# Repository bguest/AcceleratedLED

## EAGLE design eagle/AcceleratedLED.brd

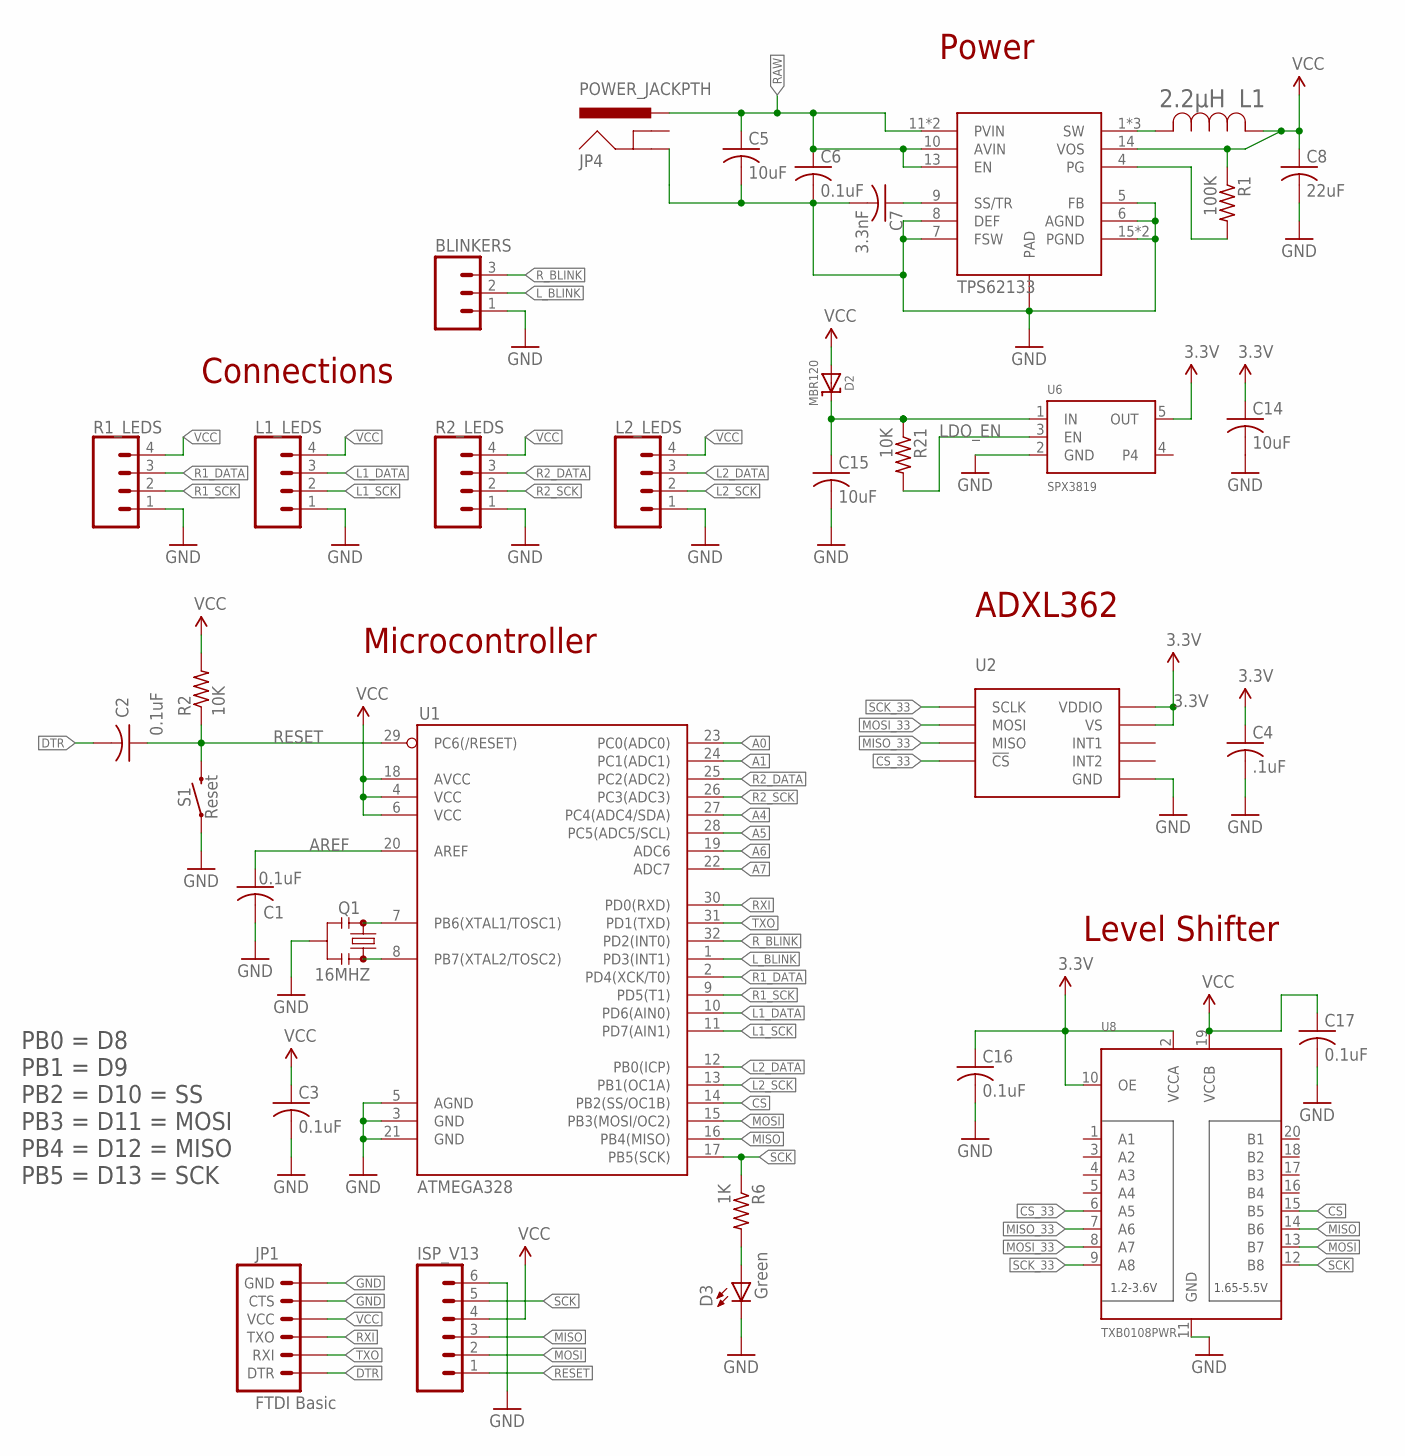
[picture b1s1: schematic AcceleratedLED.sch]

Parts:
BLINKERS: M03JST-PTH; JST-3-PTH
C1, C2, C3, C6, C16, C17: 0.1uF; C0805
C4: .1uF; C0805
C5, C14, C15: 10uF; C0805
C7: 3.3nF; C0805
C8: 22uF; C0805
D2: MBR120; SOD-123
D3: Green; CHIPLED_0805
IC1: TPS62133; QFN16
ISP_V13: M06SIP; 1X06
JP1: FTDI Basic; 1X06
JP4: POWER_JACKPTH; POWER_JACK_PTH
L1: 2.2μH; IND_IHLP-1212BZ-L
L1_LEDS, L2_LEDS: CONN_04JST-PTH; JST-4-PTH
Q1: 16MHZ; RESONATOR-SMD
R1: 100K; M0805
R1_LEDS, R2_LEDS: CONN_04JST-PTH; JST-4-PTH
R2, R21: 10K; M0805
R6: 1K; M0805
S1: Reset; TACTILE_SWITCH_SMD_5.2MM
U1: ATMEGA328; TQFP32-08
U2: ADXL362ADXL362-1:1; ADXL362-1:1
U6: SPX3819; SOT23-5
U8: TXB0108PWR; TSSOP20

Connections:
3.3V: C4.1, C14.1, C16.1, U2.P$1 (VDDIO), U2.P$14 (VS), U6.5 (OUT), U8.2 (VCCA), U8.10 (OE)
A0: U1.23 (PC0(ADC0))
A1: U1.24 (PC1(ADC1))
A4: U1.27 (PC4(ADC4/SDA))
A5: U1.28 (PC5(ADC5/SCL))
A6: U1.19 (ADC6)
A7: U1.22 (ADC7)
AREF: C1.1, U1.20 (AREF)
CS: U1.14 (PB2(SS/OC1B)), U8.15 (B5)
CS_33: U2.P$8 (!CS), U8.6 (A5)
DTR: C2.2, JP1.1 (DTR)
GND: BLINKERS.1, C1.2, C3.2, C4.2, C5.2, C6.2, C7.2, C8.2, C14.2, C15.2, C16.2, C17.2, D3.C, IC1.5 (FB), IC1.6 (AGND), IC1.7 (FSW), IC1.8 (DEF), IC1.15 (PGND), IC1.16 (PGND), IC1.PAD, ISP_V13.6, JP1.5 (CTS), JP1.6 (GND), JP4.GND, L1_LEDS.1, L2_LEDS.1, Q1.2, R1_LEDS.1, R2_LEDS.1, S1.1, S1.2 (1), U1.3 (GND), U1.5 (AGND), U1.21 (GND), U2.P$12 (GND), U2.P$13 (GND), U2.P$16 (GND), U6.2 (GND), U8.11 (GND)
L1_DATA: L1_LEDS.3, U1.10 (PD6(AIN0))
L1_SCK: L1_LEDS.2, U1.11 (PD7(AIN1))
L2_DATA: L2_LEDS.3, U1.12 (PB0(ICP))
L2_SCK: L2_LEDS.2, U1.13 (PB1(OC1A))
LDO_EN: R21.2, U6.3 (EN)
L_BLINK: BLINKERS.2, U1.1 (PD3(INT1))
MISO: ISP_V13.3, U1.16 (PB4(MISO)), U8.14 (B6)
MISO_33: U2.P$7 (MISO), U8.7 (A6)
MOSI: ISP_V13.2, U1.15 (PB3(MOSI/OC2)), U8.13 (B7)
MOSI_33: U2.P$6 (MOSI), U8.8 (A7)
unnamed: Q1.3, U1.8 (PB7(XTAL2/TOSC2))
unnamed: Q1.1, U1.7 (PB6(XTAL1/TOSC1))
unnamed: D3.A, R6.2
unnamed: C15.1, D2.C, R21.1, U6.1 (IN)
PG: IC1.4 (PG), R1.2
R1_DATA: R1_LEDS.3, U1.2 (PD4(XCK/T0))
R1_SCK: R1_LEDS.2, U1.9 (PD5(T1))
R2_DATA: R2_LEDS.3, U1.25 (PC2(ADC2))
R2_SCK: R2_LEDS.2, U1.26 (PC3(ADC3))
RAW: C5.1, C6.1, IC1.10 (AVIN), IC1.11 (PVIN), IC1.12 (PVIN), IC1.13 (EN), JP4.PWR
RESET: C2.1, ISP_V13.1, R2.1, S1.3 (2), S1.4 (2), U1.29 (PC6(/RESET))
RXI: JP1.3 (TXO), U1.30 (PD0(RXD))
R_BLINK: BLINKERS.3, U1.32 (PD2(INT0))
SCK: ISP_V13.5, R6.1, U1.17 (PB5(SCK)), U8.12 (B8)
SCK_33: U2.P$4 (SCLK), U8.9 (A8)
SS/TR: C7.1, IC1.9 (SS/TR)
SW: IC1.1 (SW), IC1.2 (SW), IC1.3 (SW), L1.2
TXO: JP1.2 (RXI), U1.31 (PD1(TXD))
VCC: C3.1, C8.1, C17.1, D2.A, IC1.14 (VOS), ISP_V13.4, JP1.4 (VCC), L1.1, L1_LEDS.4, L2_LEDS.4, R1.1, R1_LEDS.4, R2.2, R2_LEDS.4, U1.4 (VCC), U1.6 (VCC), U1.18 (AVCC), U8.19 (VCCB)

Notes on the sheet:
Microcontroller
Level Shifter
ADXL362
Connections
PB0 = D8 PB1 = D9 PB2 = D10 = SS PB3 = D11 = MOSI PB4 = D12 = MISO PB5 = D13 = SCK
Power

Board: 2 copper layers, 34 parts (0 on the bottom side), 35 nets, no tracks yet.

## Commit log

2018-09-08 Add switching power
2018-10-10 small board changes
2018-10-17 Add Accelerometer class
2018-10-17 Add BottomUp Effect
2018-10-23 Switch to DotStar
2018-11-06 Add Bumps effects
2018-11-13 Add Bumps
2018-12-10 Move to support R1,L1,R2,L2 strands
2019-01-11 Add Sign & Segments

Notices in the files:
parts and their libraries:
SparkFun-Sensors: Licensing: CC v3.0 Share-Alike You are welcome to use this library for commercial purposes.
SparkFun-Connectors: Licensing: Creative Commons ShareAlike 4.0 International - https://creativecommons.org/licenses/by-sa/4.0
